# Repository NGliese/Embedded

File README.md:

# Embedded Repo
This repository is a collection of hobby projects by Nikolaj Gliese Pedersen.

The collection is divided into three subfolders: 

**Library**; Collection of portable c++ projects for use in the "real projects" <br>
- Every project in the library collection is unit testet using cpputest. We are not fully TDD complient, 
  but for the most part: _this is they way._ <br>
  -- see https://github.com/NGliese/Embedded/tree/master/library

**Linux**; linux-based projects such as security system based on movement detection <br>
- Every linux based project has an integration test enviroment. As an example rpiCam has a integration test class called RPICam_Capture, which
only objective is to make sure that when we call RPICam_Capture::stream() we can see that there is a connection to the rpi cam. <br>
 -- see https://github.com/NGliese/Embedded/tree/master/linux/RPI/OutDoorMain_CCTV

**Bare_Metal**; esp32 based projects such as motor controlled dogfeeder project <br>
- Every esp32 based project containes an integration test enviroment. This enviroment is used during development to make small subparts of the full project and to easily switch between different states in a given system to make sure everything is working as inteded.<br>
-- see https://github.com/NGliese/Embedded/tree/master/baremetal/DogFeeder

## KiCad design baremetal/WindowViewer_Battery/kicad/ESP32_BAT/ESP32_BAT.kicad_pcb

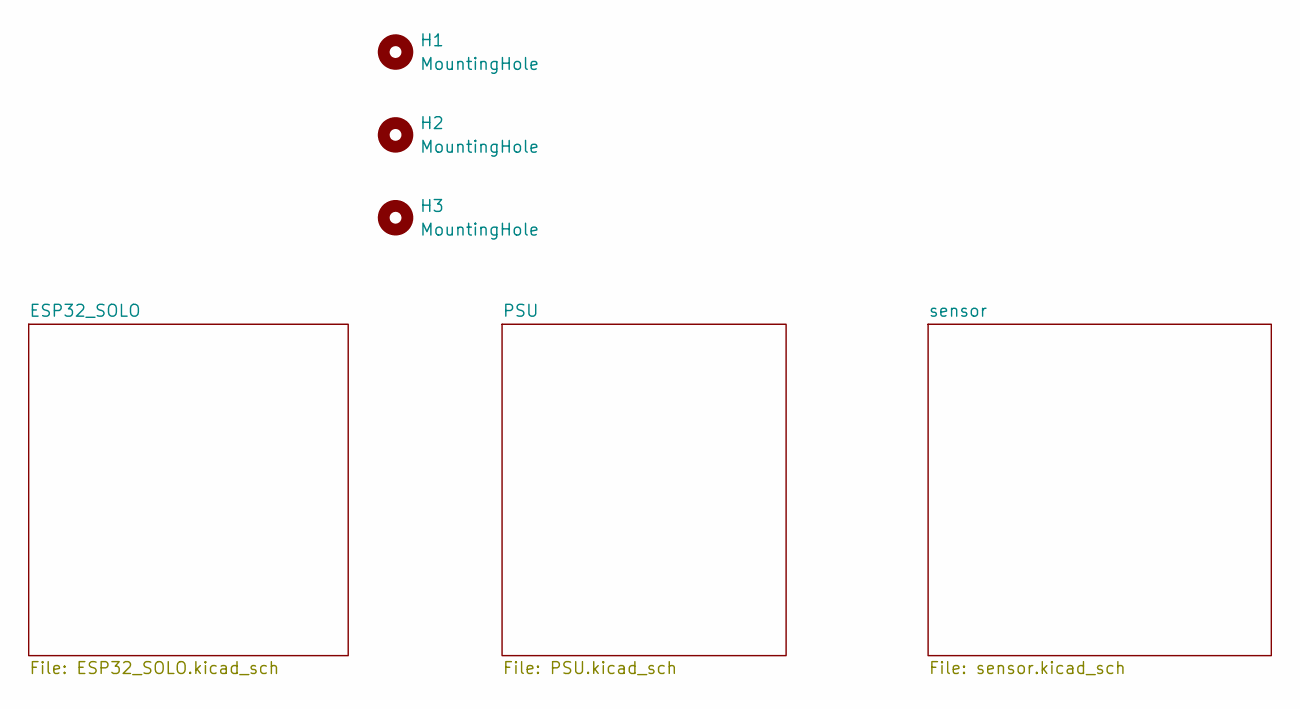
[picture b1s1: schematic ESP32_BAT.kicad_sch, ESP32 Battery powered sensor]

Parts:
H1, H2, H3: MountingHole; MountingHole_2.2mm_M2_DIN965

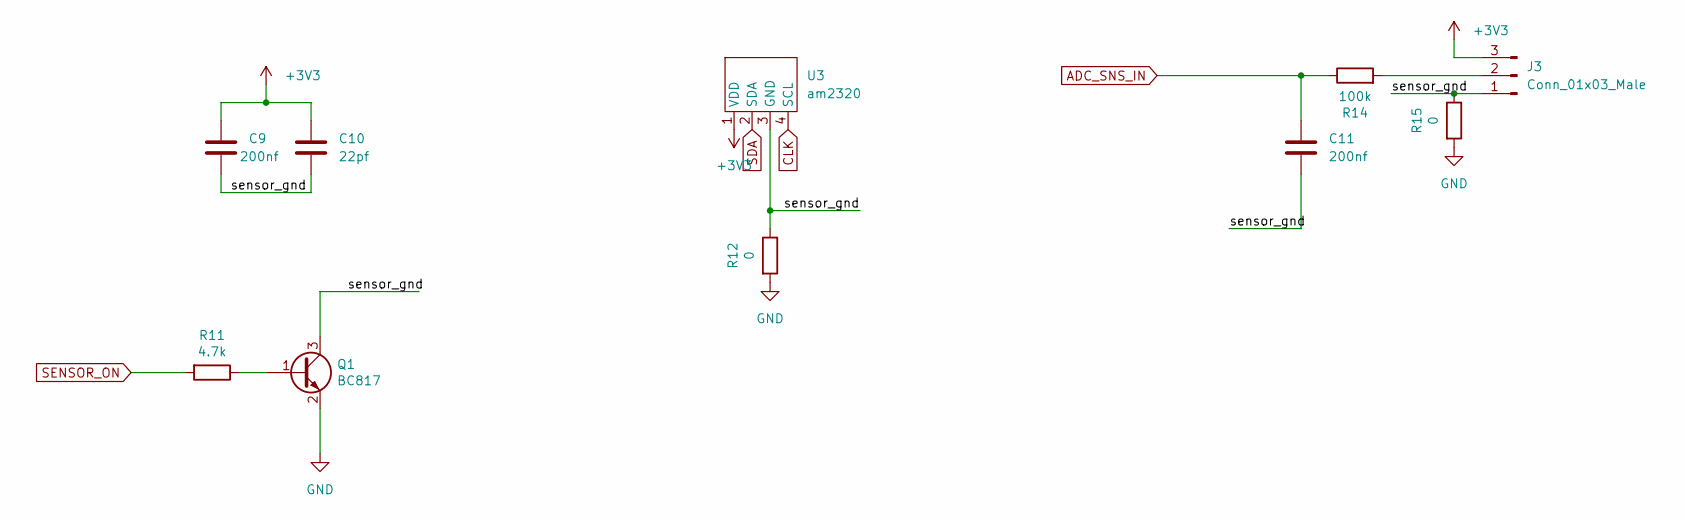
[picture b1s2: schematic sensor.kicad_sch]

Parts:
C9, C11: 200nf; C_1206_3216Metric_Pad1.33x1.80mm_HandSolder
C10: 22pf; C_1206_3216Metric_Pad1.33x1.80mm_HandSolder
J3: Conn_01x03_Male; PinHeader_1x03_P2.54mm_Vertical
Q1: BC817; SOT-23
R11: 4.7k; R_1206_3216Metric_Pad1.30x1.75mm_HandSolder
R12, R15: 0; R_1206_3216Metric_Pad1.30x1.75mm_HandSolder
R14: 100k; R_1206_3216Metric_Pad1.30x1.75mm_HandSolder
U3: am2320; PinHeader_1x04_P2.54mm_Vertical

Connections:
/sensor/sensor_gnd: C9.2, C10.2, C11.2, J3.1, Q1.3 (C), R12.1, R15.1, U3.3 (GND)
ADC_SNS_IN: C11.1, R14.1; also elsewhere on the board
CLK: U3.4 (SCL); also elsewhere on the board
GND: Q1.2 (E), R12.2, R15.2; also elsewhere on the board
unnamed: J3.2, R14.2
unnamed: Q1.1 (B), R11.1
SDA: U3.2 (SDA); also elsewhere on the board
SENSOR_ON: R11.2; also elsewhere on the board

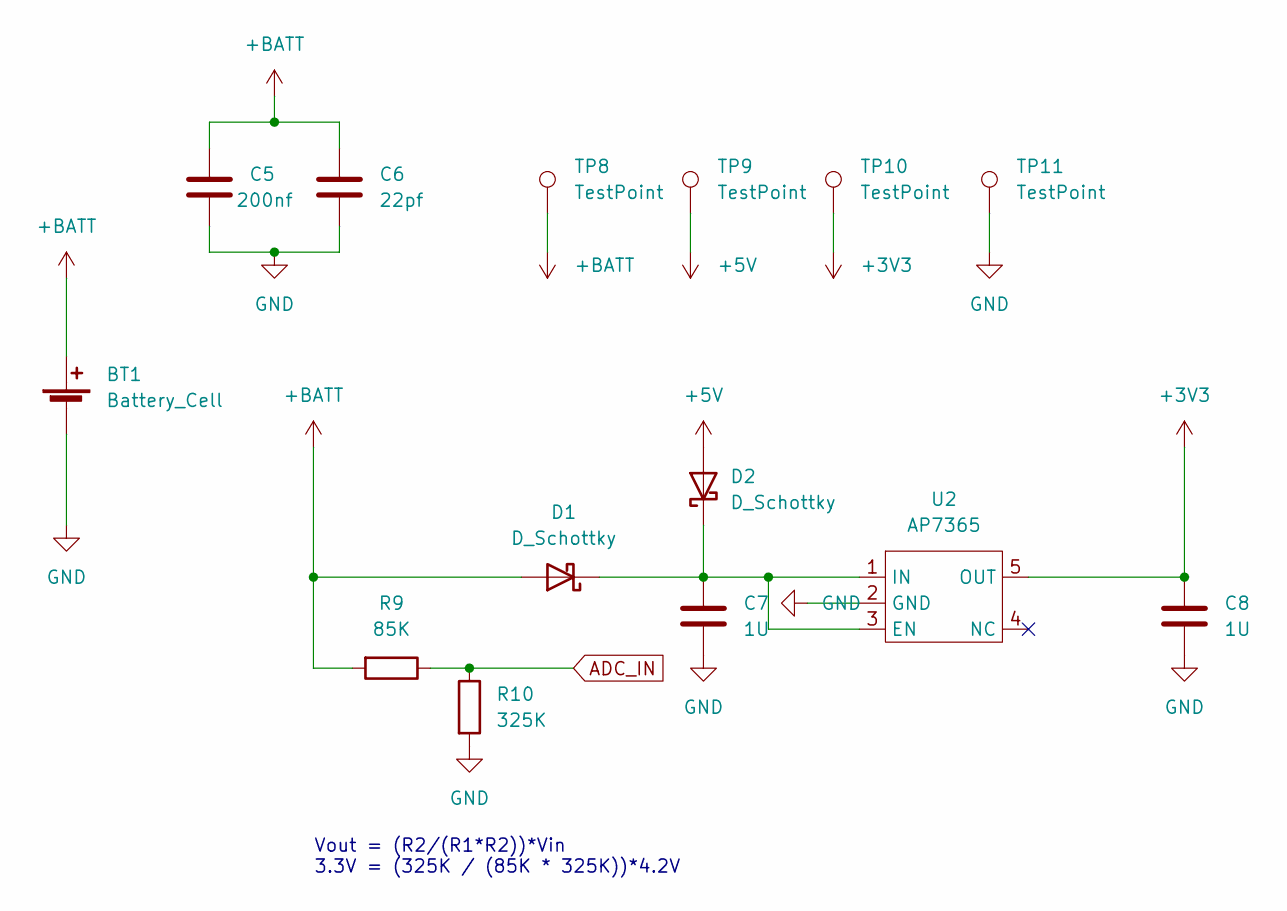
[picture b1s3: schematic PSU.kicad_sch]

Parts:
BT1: Battery_Cell; AA_BATTERYCASE_2460
C5: 200nf; C_1206_3216Metric_Pad1.33x1.80mm_HandSolder
C6: 22pf; C_1206_3216Metric_Pad1.33x1.80mm_HandSolder
C7, C8: 1U; C_1206_3216Metric_Pad1.33x1.80mm_HandSolder
D1, D2: D_Schottky; CUS10S30
R9: 85K; R_1206_3216Metric_Pad1.30x1.75mm_HandSolder
R10: 325K; R_1206_3216Metric_Pad1.30x1.75mm_HandSolder
TP8, TP9, TP10, TP11: TestPoint; TestPoint_Pad_2.5x2.5mm
U2: AP7365; TSOP-5_1.65x3.05mm_P0.95mm

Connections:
+5V: D2.2 (A), TP9.1; also elsewhere on the board
+BATT: BT1.1 (+), C5.1, C6.1, D1.2 (A), R9.2, TP8.1
ADC_IN: R9.1, R10.1; also elsewhere on the board
GND: BT1.2 (-), C5.2, C6.2, C7.2, C8.2, R10.2, TP11.1, U2.2 (GND); also elsewhere on the board
unnamed: C7.1, D1.1 (K), D2.1 (K), U2.1 (IN), U2.3 (EN)

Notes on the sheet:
Vout = (R2/(R1*R2))*Vin 3.3V = (325K / (85K * 325K))*4.2V

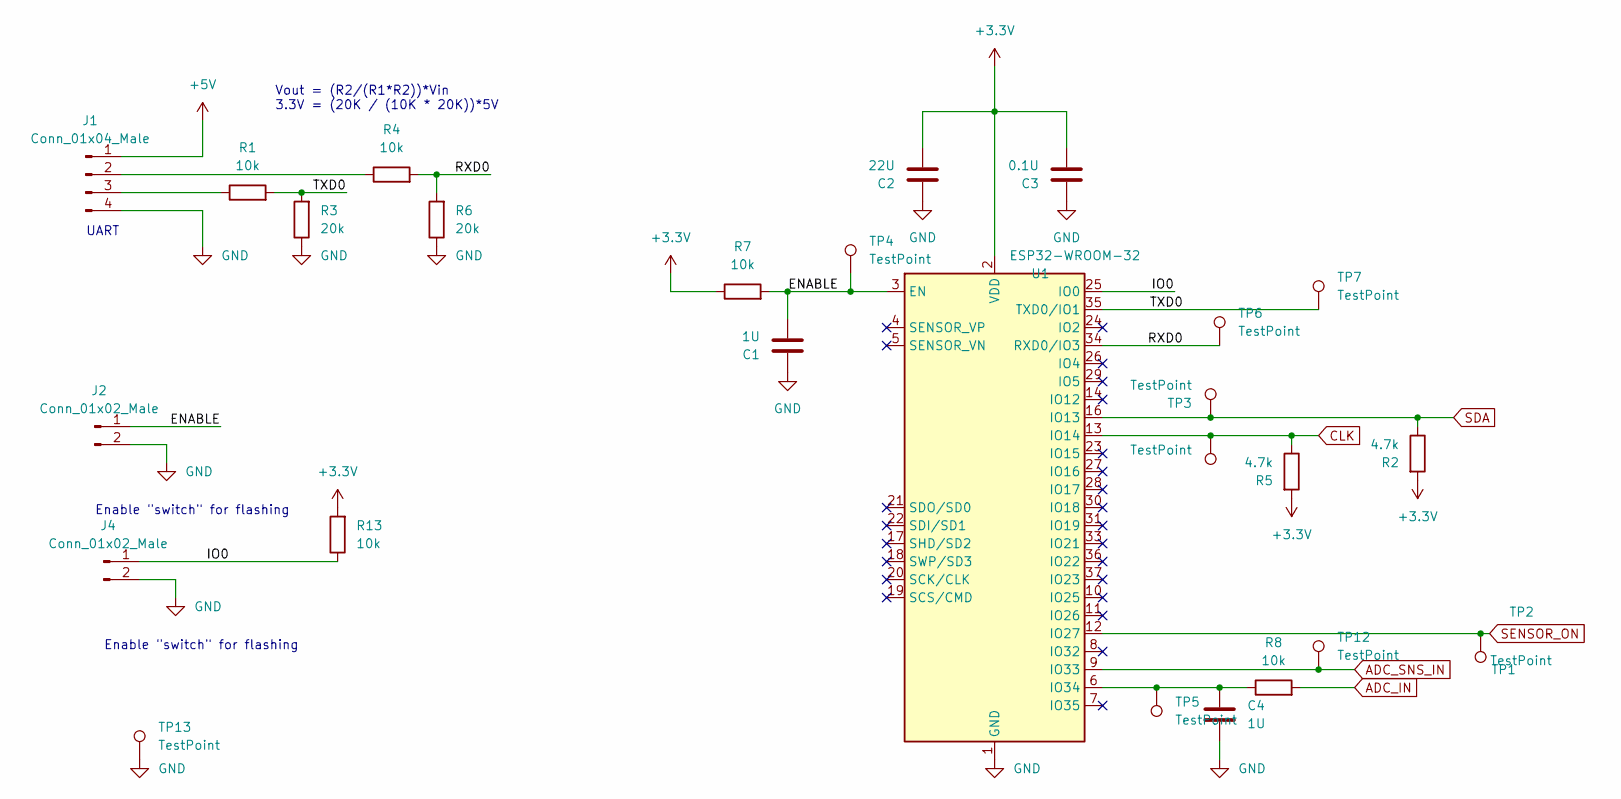
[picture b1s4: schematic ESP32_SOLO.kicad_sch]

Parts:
C1, C4: 1U; C_1206_3216Metric_Pad1.33x1.80mm_HandSolder
C2: 22U; C_1206_3216Metric_Pad1.33x1.80mm_HandSolder
C3: 0.1U; C_1206_3216Metric_Pad1.33x1.80mm_HandSolder
J1: Conn_01x04_Male; PinHeader_1x04_P2.54mm_Vertical
J2, J4: Conn_01x02_Male; PinHeader_1x02_P2.54mm_Vertical
R1, R4, R7, R8, R13: 10k; R_1206_3216Metric_Pad1.30x1.75mm_HandSolder
R2, R5: 4.7k; R_1206_3216Metric_Pad1.30x1.75mm_HandSolder
R3, R6: 20k; R_1206_3216Metric_Pad1.30x1.75mm_HandSolder
TP1, TP2, TP3, TP4, TP5, TP6, TP7, TP12, TP13: TestPoint; PinHeader_1x01_P2.54mm_Vertical
U1: ESP32-WROOM-32

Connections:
+5V: J1.1; also elsewhere on the board
/ESP32_SOLO/ENABLE: C1.2, J2.1, R7.2, TP4.1, U1.3 (EN)
/ESP32_SOLO/IO0: J4.1, R13.1, U1.25 (IO0)
/ESP32_SOLO/RXD0: R4.2, R6.2, TP6.1, U1.34 (RXD0/IO3)
/ESP32_SOLO/TXD0: R1.2, R3.2, TP7.1, U1.35 (TXD0/IO1)
ADC_IN: R8.2; also elsewhere on the board
ADC_SNS_IN: TP12.1, U1.9 (IO33); also elsewhere on the board
CLK: R5.1, TP2.1, U1.13 (IO14); also elsewhere on the board
GND: C1.1, C2.1, C3.1, C4.2, J1.4, J2.2, J4.2, R3.1, R6.1, TP13.1, U1.1 (GND), U1.15 (GND), U1.38 (GND), U1.39 (GND); also elsewhere on the board
unnamed: C4.1, R8.1, TP5.1, U1.6 (IO34)
unnamed: J1.2, R4.1
unnamed: J1.3, R1.1
SDA: R2.1, TP3.1, U1.16 (IO13); also elsewhere on the board
SENSOR_ON: TP1.1, U1.12 (IO27); also elsewhere on the board

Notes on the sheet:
Enable "switch" for flashing
Vout = (R2/(R1*R2))*Vin 3.3V = (20K / (10K * 20K))*5V
UART

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
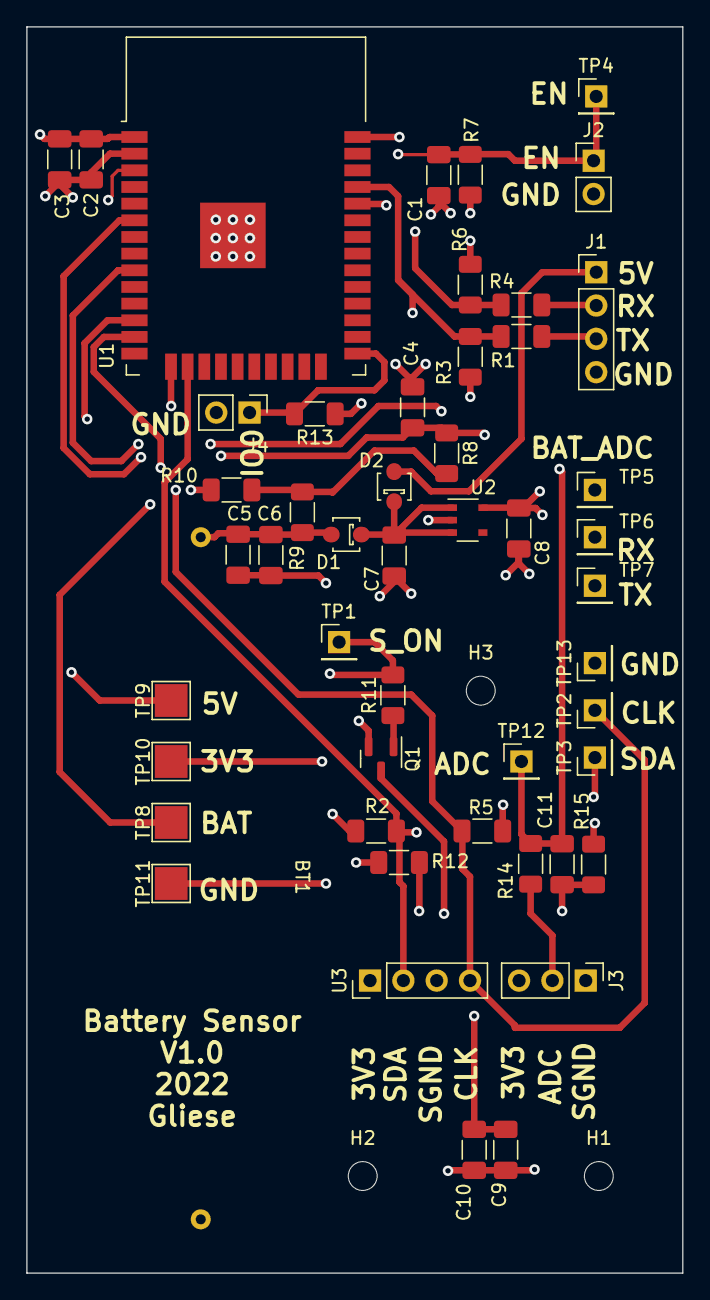
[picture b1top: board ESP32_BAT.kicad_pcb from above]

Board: 4 copper layers, 50.0 x 95.0 mm, 53 parts (0 on the bottom side), 20 nets.

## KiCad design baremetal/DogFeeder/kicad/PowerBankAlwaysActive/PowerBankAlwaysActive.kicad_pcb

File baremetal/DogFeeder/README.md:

# DogFeeder Repo

In a not so far future, our dog will be home alone for +8 hours.
Some of the residense fear that our dog will be lonely and therefor the need for some active toys which can be fully automated to start at given periods throughout the day.

## The dogfeeder project
This project is ment to be a solution to a lonly and starving dog. The dogfeeder is required to automatically open up a door to deliever delicious dog food at specific periodes through out the day.

## Use Cases

### User wants to give the dog a treat

## Software achitecture

### ServoController

The servo controller is a class-container used for encapsulating the functionallity of activating the servo motors. 
In this project, two servo motors and two current sesnors will be used, however the ServoController will make it look like they are a single unit, for the end user.

## PCB board
The PCB board developed is ment to support a esp32-dev board with up to 3 actuators powered by an external power source. The board is a 4-layer board and is created through the opensource project https://www.kicad.org/

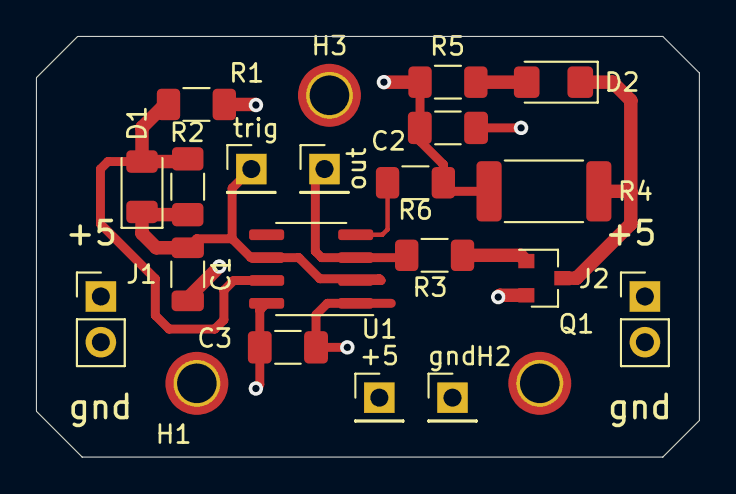
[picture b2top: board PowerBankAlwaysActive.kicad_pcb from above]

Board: 4 copper layers, 36.8 x 23.4 mm, 22 parts (0 on the bottom side), 9 nets.

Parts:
+5: TestPoint; PinHeader_1x01_P2.54mm_Vertical
C1: 10uf; C_1206_3216Metric
C2, C3: 4.7uf; C_1206_3216Metric_Pad1.33x1.80mm_HandSolder
D1: D; D_1206_3216Metric
D2: LED; LED_1206_3216Metric_Pad1.42x1.75mm_HandSolder
H1, H2, H3: MountingHole; MountingHole_2.2mm_M2_ISO7380_Pad_TopBottom
J1, J2: Conn_01x02_Female; PinHeader_1x02_P2.54mm_Vertical
Q1: BC817; SOT-23
R1: 220k; R_1206_3216Metric_Pad1.30x1.75mm_HandSolder
R2: 3.3M; R_1206_3216Metric_Pad1.30x1.75mm_HandSolder
R3: 4.7k; R_1206_3216Metric_Pad1.30x1.75mm_HandSolder
R4: 51; R_2512_6332Metric_Pad1.40x3.35mm_HandSolder
R5: 330; R_1206_3216Metric_Pad1.30x1.75mm_HandSolder
R6: 0R; R_1206_3216Metric_Pad1.30x1.75mm_HandSolder
U1: ICM7555xB; SOIC-8_3.9x4.9mm_P1.27mm
gnd: TestPoint; PinHeader_1x01_P2.54mm_Vertical
out: TestPoint; PinHeader_1x01_P2.54mm_Vertical
trig: TestPoint; PinHeader_1x01_P2.54mm_Vertical

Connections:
+5V: +5.1, C2.1, C3.1, J1.1, J2.1, R1.1, R4.2, R5.1, R6.2, U1.8
/disch: D1.2, R1.2, R2.1, U1.7
/output: R3.2, U1.3, out.1
/trig: C1.1, D1.1, R2.2, U1.2, U1.6, trig.1
GND: C1.2, C2.2, C3.2, J1.2, J2.2, Q1.2, U1.1, gnd.1
unnamed: D2.1, Q1.3, R4.1
unnamed: D2.2, R5.2
unnamed: Q1.1, R3.1
unnamed: R6.1, U1.4

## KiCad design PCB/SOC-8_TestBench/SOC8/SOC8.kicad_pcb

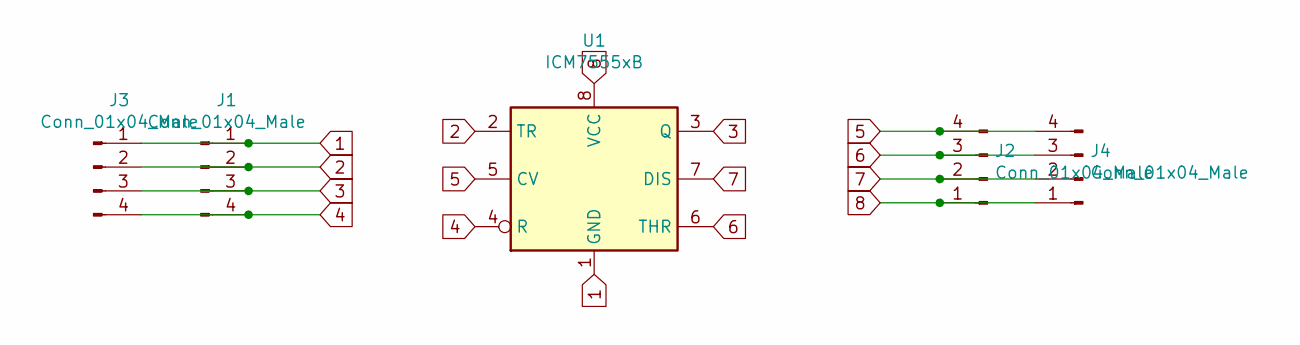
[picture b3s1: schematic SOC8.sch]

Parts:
J1, J2, J3, J4: Conn_01x04_Male; PinHeader_1x04_P2.54mm_Vertical
U1: ICM7555xB; SOIC-8_3.9x4.9mm_P1.27mm

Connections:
1: J1.1, J3.1, U1.1 (GND)
2: J1.2, J3.2, U1.2 (TR)
3: J1.3, J3.3, U1.3 (Q)
4: J1.4, J3.4, U1.4 (R)
5: J2.4, J4.4, U1.5 (CV)
6: J2.3, J4.3, U1.6 (THR)
7: J2.2, J4.2, U1.7 (DIS)
8: J2.1, J4.1, U1.8 (VCC)

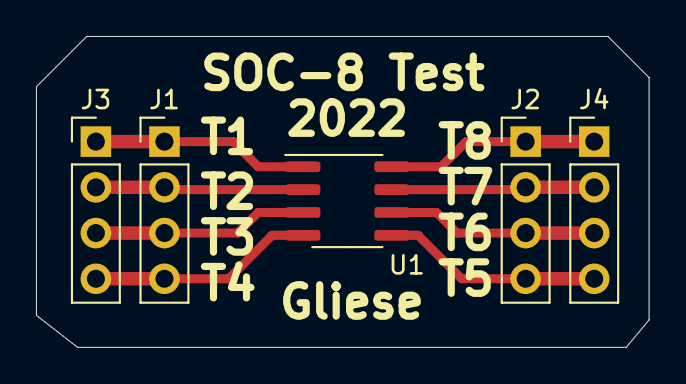
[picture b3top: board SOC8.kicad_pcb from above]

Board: 2 copper layers, 34.0 x 17.3 mm, 5 parts (0 on the bottom side), 8 nets.

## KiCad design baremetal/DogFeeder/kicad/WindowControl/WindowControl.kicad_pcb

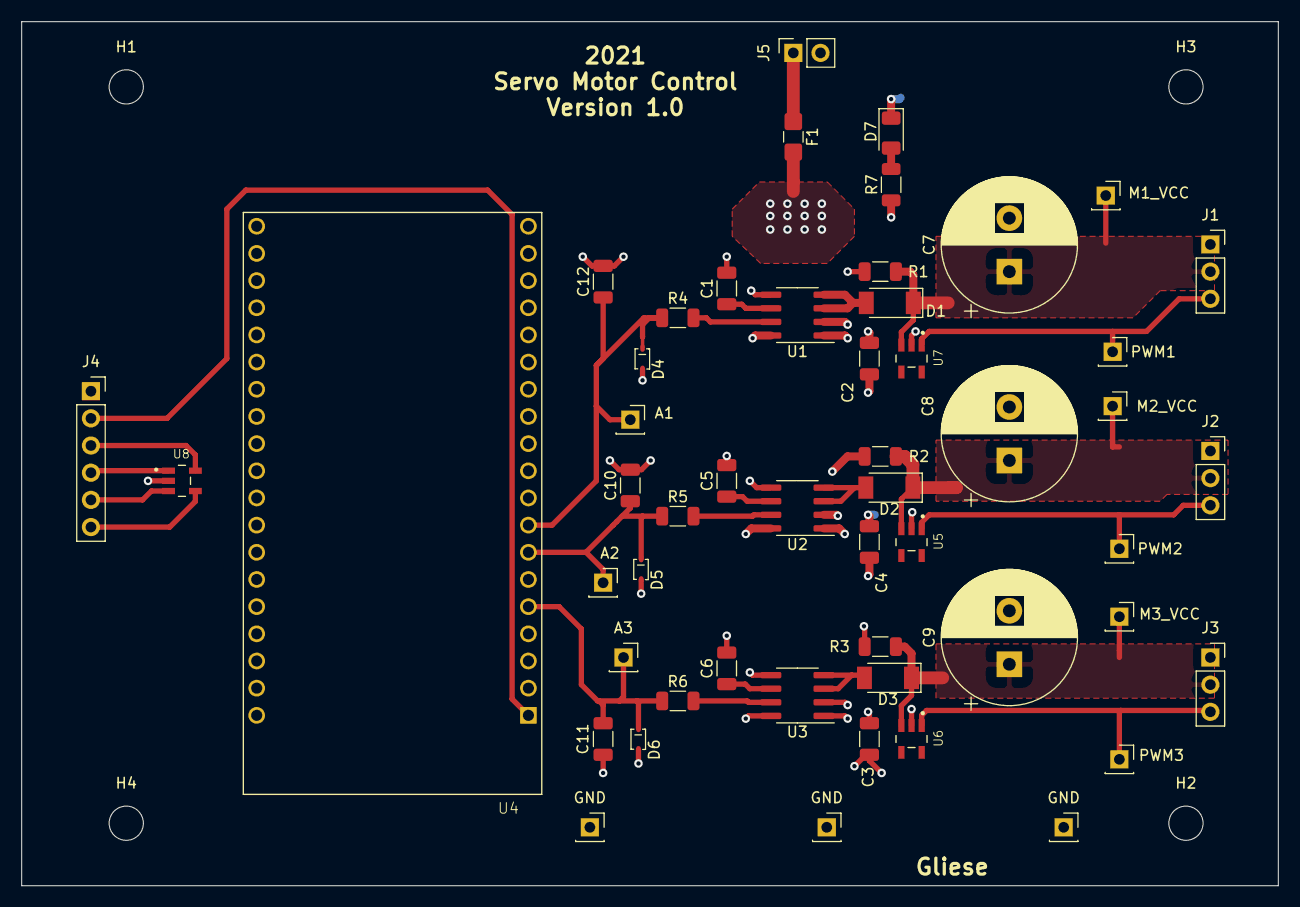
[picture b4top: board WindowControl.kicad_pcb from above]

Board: 4 copper layers, 117.5 x 80.8 mm, 56 parts (0 on the bottom side), 27 nets.

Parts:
A1, A2, A3: TestPoint; PinSocket_1x01_P2.54mm_Vertical
C1, C5, C6, C11: 0.1uf; C_1206_3216Metric
C2, C3, C4: 200nf; C_1206_3216Metric
C7, C8, C9: C; CP_Radial_D12.5mm_P5.00mm
C10, C12: C; C_1206_3216Metric
D1, D2, D3: D_Schottky; D_SOD-128
D4, D5, D6: D_Zener; DDZ3V6ASF-7
D7: LED; LED_1206_3216Metric
F1: Fuse; Fuse_1206_3216Metric_Castellated
GND: TestPoint; PinSocket_1x01_P2.54mm_Vertical
GND#2, GND#3: TestPoint; PinSocket_1x01_P2.54mm_Vertical
H1, H2, H3, H4: MountingHole_Pad; MountingHole_3.2mm_M3_ISO14580
J1, J2, J3: Screw_Terminal_01x03; PinSocket_1x03_P2.54mm_Vertical
J4: Conn_01x06_Male; PinSocket_1x06_P2.54mm_Vertical
J5: Screw_Terminal_01x02; PinSocket_1x02_P2.54mm_Vertical
M1_VCC, M2_VCC, M3_VCC: TestPoint; PinSocket_1x01_P2.54mm_Vertical
PWM1, PWM2, PWM3: TestPoint; PinSocket_1x01_P2.54mm_Vertical
R1, R2, R3: 1M; R_1206_3216Metric
R4, R5, R6: 4.7k; R_1206_3216Metric
R7: 500; R_1206_3216Metric
U1, U2, U3: ACS724xLCTR-05AB; SOIC-8_3.9x4.9mm_P1.27mm
U4: ESP32-DEVKITC-32D; MODULE_ESP32-DEVKITC-32D
U5, U6, U7, U8: ESDS314DBVR; SOT95P280X145-5N

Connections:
+3V3: J4.2, U4.1
+5VD: C2.1, C3.1, C4.1, F1.2, R7.1, U1.1, U1.2, U1.8, U2.1, U2.2, U2.8, U3.1, U3.2, U3.8
Current_Sensor_1_AOUT: A1.1, C12.1, D4.1, R4.1, U4.8
Current_Sensor_2_AOUT: A2.1, C10.1, D5.1, R5.1, U4.7
Current_Sensor_3_AOUT: A3.1, C11.1, D6.1, R6.1, U4.5
GND: C1.2, C2.2, C3.2, C4.2, C5.2, C6.2, C7.2, C8.2, C9.2, C10.2, C11.2, C12.2, D4.2, D5.2, D6.2, D7.1, GND.1, GND#2.1, GND#3.1, J1.1, J2.1, J3.1, J4.1, J5.2, R1.2, R2.2, R3.2, U1.5, U2.5, U3.5, U4.14, U4.20, U4.26, U5.2, U6.2, U7.2, U8.2
IO1: J4.6, U4.21, U8.4
IO2: J4.5, U4.22, U8.3
IO3: J4.4, U4.25, U8.1
IO4: J4.3, U4.28, U8.5
unnamed: C1.1, U1.6
unnamed: C5.1, U2.6
unnamed: C6.1, U3.6
unnamed: C7.1, D1.1, J1.2, M1_VCC.1, R1.1, U7.3
unnamed: C8.1, D2.1, J2.2, M2_VCC.1, R2.1, U5.3
unnamed: C9.1, D3.1, J3.2, M3_VCC.1, R3.1, U6.3
unnamed: D1.2, U1.3, U1.4
unnamed: D2.2, U2.3, U2.4
unnamed: D3.2, U3.3, U3.4
unnamed: D7.2, R7.2
unnamed: F1.1, J5.1
unnamed: R4.2, U1.7
unnamed: R5.2, U2.7
unnamed: R6.2, U3.7
PWM1: J1.3, PWM1.1, U4.11, U7.1
PWM2: J2.3, PWM2.1, U4.10, U5.1
PWM3: J3.3, PWM3.1, U4.9, U6.1

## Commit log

2021-09-04 init
2021-09-04 cctv info
2021-09-04 images for cctv
2021-09-04 gif demo of cctv
2021-09-04 lib readme
2021-09-04 template for esp32
2021-09-04 dogfeeder project 0.1
2021-09-04 dogfeeder readme
2021-09-04 Create LICENSE
2021-09-11 commit message
2021-09-11 removed build files from pwm test
2021-09-11 removed build files from gpio test
2021-09-12 pwm + fault handler finished
2021-09-12 create depabot
2021-09-20 pwm test 1.0
2021-09-21 adc 0.1, issues with readings test OK
2021-09-22 adc fixed
2021-09-25 doxygen comments added
2021-10-10 codeql analysis
2021-10-10 diagrams for servocontroller
2021-10-10 servo motor w. tests
2021-11-16 rules added to cctv to only post slack alarms in the night time
2021-11-23 Door api init @servo motor open / close functionality finished @servo motor test cases finished @todo addin current sensor logic
2021-12-14 cctv update : rules for vaccation dogfeeder update: documentation of use case - feed the dog
2021-12-14 name update
2021-12-18 pcb board : power bank hack v1.0 included
2021-12-18 frontend for dogfeeder started
2021-12-19 GUI http update
2021-12-30 CI/CD integration.
    We are now able to format code, use sanitizer, code complexity, cppcheck clang-tidy check and unittest every part of the library code
    Targets installed : esp32 and RPI4B
2021-12-31 frontend update : node-red http requests included
2022-01-06 update to cctv & test-pcb board
2022-01-07 database restructure -> sensor and datapoint alignment
2022-01-07 HTTP for esp32 v0.5. Needs testing
2022-01-08 esp32_http get protocol v0.75
    fixed:
    threadsafe
    http-call
    output in str format
    missing:
    str2Json
2022-01-08 cleaned up the esp32_http protocol and fixed react bug
2022-01-09 JSON object added to project
2022-01-09 outdoor cctv docs update
2022-01-09 coverage included
2022-01-09 moved docs and report to seperat github.io
2022-01-09 docs moved to seperat io
2022-01-15 finalized powerbank-actiavtor
2022-01-17 JSMN implementation to lib
    We saw issues with esp32 and full lib of json so we will try to implement the simple
    version, jsmn, instead.
2022-01-22 dogfeeder 1.0
    running battery test : NOT OPTIMIZED esp32
2022-01-26 updates to init motor -> bug in start value @ ctor
    battery test for dogfeeder, deep-sleep with memory.
2022-01-29 included format for targets
2022-01-29 readme update
2022-01-29 moved docs
2022-01-29 moved docs again
2022-01-29 doxygen theme update
2022-02-14 pcb for window detector started
2022-02-19 battery pcb update, schematic done
2022-02-24 watersensor 0.1
2022-02-27 watersensor
2022-02-27 watersensor docs
2022-02-27 sensor controller setup
2022-03-05 databroker v1.0
2022-03-06 serviceBase up and running
2022-03-15 service_base 1.0
2022-03-18 service - broker dependencies OK
2022-03-18 hardware test 0.1
2022-03-20 watermeter setup 1.0
2022-04-09 i2c started
